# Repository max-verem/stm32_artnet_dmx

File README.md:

# STM32 Art-Net gateway for DMX512

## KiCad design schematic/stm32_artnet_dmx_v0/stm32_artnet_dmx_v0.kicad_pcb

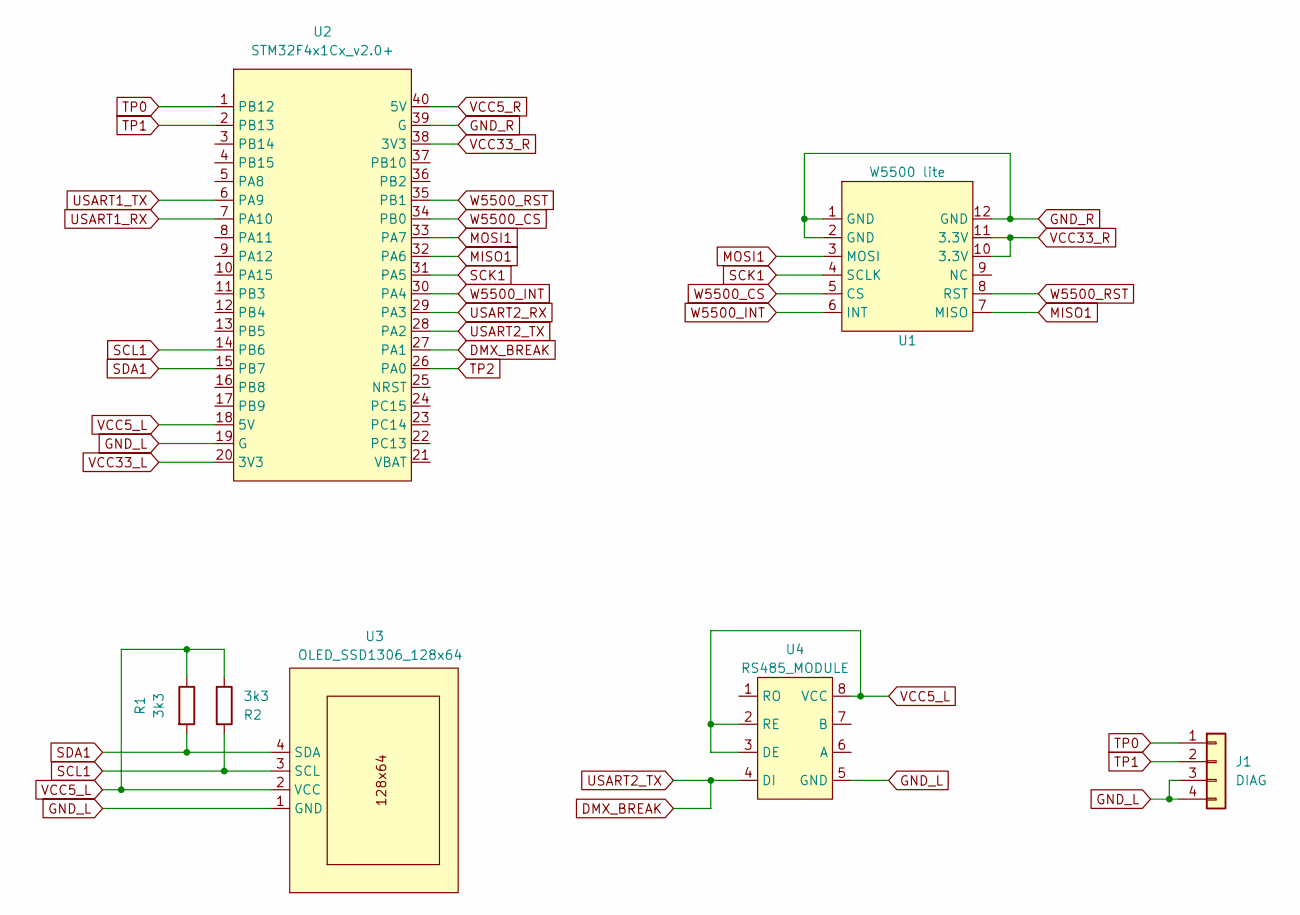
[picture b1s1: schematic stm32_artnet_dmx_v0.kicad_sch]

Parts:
J1: DIAG; PinHeader_1x04_P2.54mm_Vertical
R1, R2: 3k3; R_Axial_DIN0204_L3.6mm_D1.6mm_P7.62mm_Horizontal
U1: W5500 lite; W5500_Lite
U2: STM32F4x1Cx_v2.0+; DIP-40_W15.24mm_LongPads
U3: OLED_SSD1306_128x64
U4: RS485_MODULE

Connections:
DMX_BREAK: U2.27 (PA1), U2.28 (PA2), U4.4 (DI)
GND_L: J1.3, J1.4, U2.19 (G), U3.1 (GND), U4.5 (GND)
GND_R: U1.1 (GND), U1.2 (GND), U1.12 (GND), U2.39 (G)
MISO1: U1.7 (MISO), U2.32 (PA6)
MOSI1: U1.3 (MOSI), U2.33 (PA7)
SCK1: U1.4 (SCLK), U2.31 (PA5)
SCL1: R2.1, U2.14 (PB6), U3.3 (SCL)
SDA1: R1.2, U2.15 (PB7), U3.4 (SDA)
TP0: J1.1, U2.1 (PB12)
TP1: J1.2, U2.2 (PB13)
TP2: U2.26 (PA0)
USART1_RX: U2.7 (PA10)
USART1_TX: U2.6 (PA9)
USART2_RX: U2.29 (PA3)
VCC5_L: R1.1, R2.2, U2.18 (5V), U3.2 (VCC), U4.2 (RE), U4.3 (DE), U4.8 (VCC)
VCC5_R: U2.40 (5V)
VCC33_L: U2.20 (3V3)
VCC33_R: U1.10 (3.3V), U1.11 (3.3V), U2.38 (3V3)
W5500_CS: U1.5 (CS), U2.34 (PB0)
W5500_INT: U1.6 (INT), U2.30 (PA4)
W5500_RST: U1.8 (RST), U2.35 (PB1)

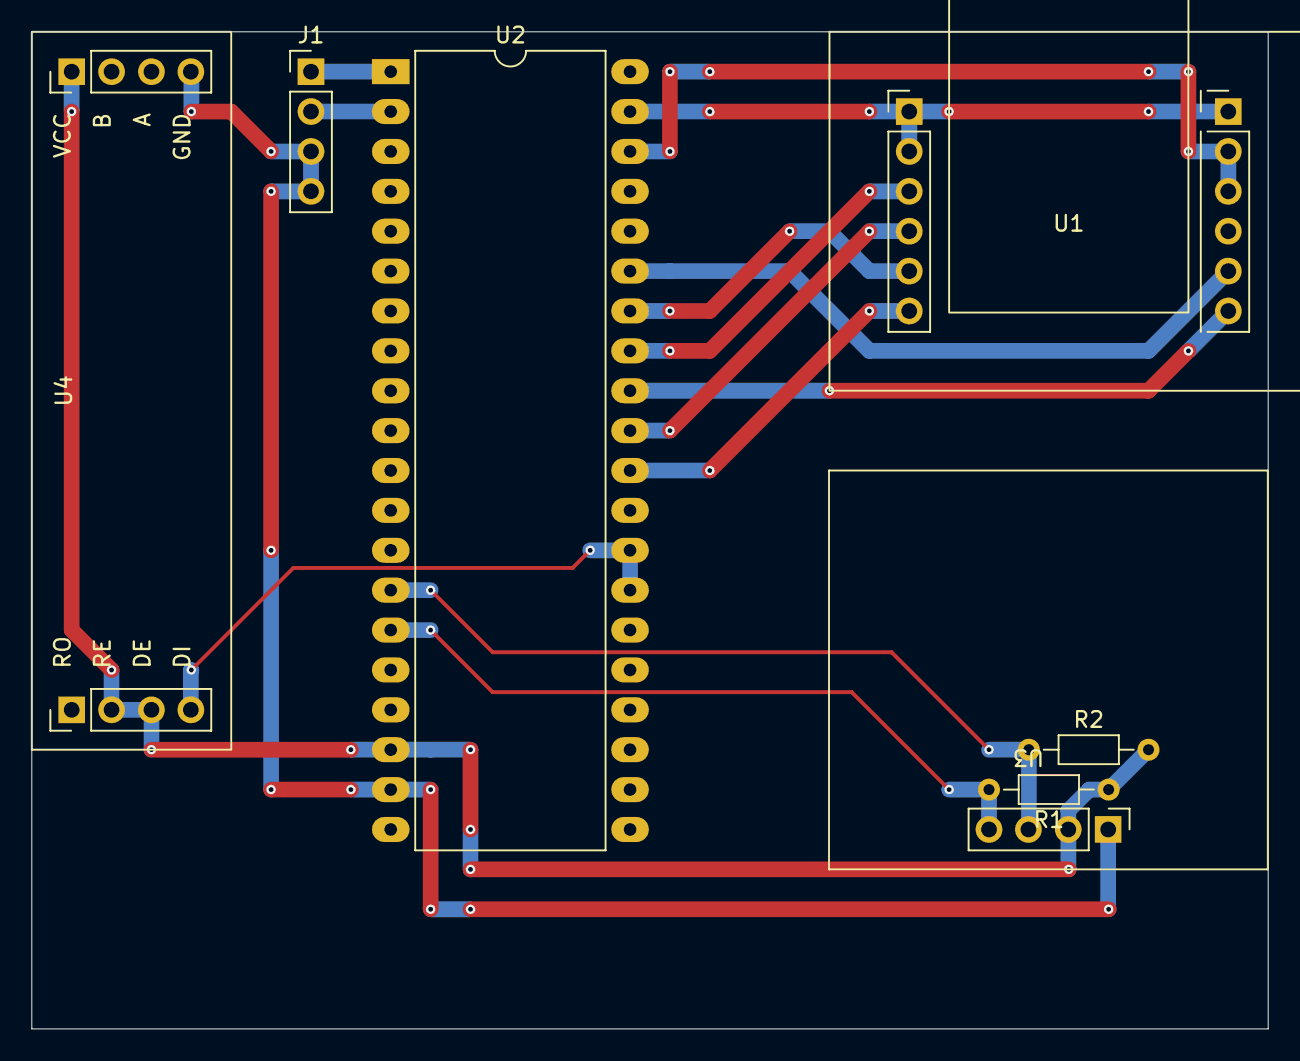
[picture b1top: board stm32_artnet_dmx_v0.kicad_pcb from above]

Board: 2 copper layers, 78.7 x 63.5 mm, 7 parts (0 on the bottom side), 15 nets.

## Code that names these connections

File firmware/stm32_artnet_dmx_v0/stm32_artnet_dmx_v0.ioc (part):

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Mcu.Name=STM32F411C(C-E)Ux
Mcu.Package=UFQFPN48
Mcu.UserName=STM32F411CEUx
PA1.GPIOParameters=GPIO_Speed,PinState,GPIO_PuPd,GPIO_Label,GPIO_ModeDefaultOutputPP
PA1.GPIO_Label=DMX_BREAK
PA1.GPIO_ModeDefaultOutputPP=GPIO_MODE_OUTPUT_OD
PA1.GPIO_PuPd=GPIO_NOPULL
PA1.GPIO_Speed=GPIO_SPEED_FREQ_VERY_HIGH
PA1.PinState=GPIO_PIN_SET
PA1.Signal=GPIO_Output
PA10.Mode=Asynchronous
PA10.Signal=USART1_RX
PA11.Mode=Device_Only
PA11.Signal=USB_OTG_FS_DM
PA12.Mode=Device_Only
PA12.Signal=USB_OTG_FS_DP
PA13.Mode=Serial_Wire
PA13.Signal=SYS_JTMS-SWDIO
PA14.Mode=Serial_Wire
PA14.Signal=SYS_JTCK-SWCLK
PA2.GPIOParameters=GPIO_ModeDefaultPP
PA2.GPIO_ModeDefaultPP=GPIO_MODE_AF_OD
PA2.Mode=Asynchronous
PA2.Signal=USART2_TX
PA3.Mode=Asynchronous
PA3.Signal=USART2_RX
PA4.GPIOParameters=GPIO_PuPd,GPIO_Label
PA4.GPIO_Label=W5500_INT
PA4.GPIO_PuPd=GPIO_PULLUP
PA4.Signal=GPXTI4
PA5.Mode=Full_Duplex_Master
PA5.Signal=SPI1_SCK
PA6.Mode=Full_Duplex_Master
PA6.Signal=SPI1_MISO
PA7.Mode=Full_Duplex_Master
PA7.Signal=SPI1_MOSI
PA9.Mode=Asynchronous
PA9.Signal=USART1_TX
PB0.GPIOParameters=GPIO_Speed,PinState,GPIO_Label
PB0.GPIO_Label=W5500_SCS
PB0.GPIO_Speed=GPIO_SPEED_FREQ_VERY_HIGH
PB0.PinState=GPIO_PIN_SET
PB0.Signal=GPIO_Output
PB1.GPIOParameters=GPIO_Speed,GPIO_Label
PB1.GPIO_Label=W5500_RST
PB1.GPIO_Speed=GPIO_SPEED_FREQ_VERY_HIGH
PB1.Signal=GPIO_Output
PB12.GPIOParameters=GPIO_Speed,GPIO_Label
PB12.GPIO_Label=TP0
PB12.GPIO_Speed=GPIO_SPEED_FREQ_VERY_HIGH
PB12.Signal=GPIO_Output
PB13.GPIOParameters=GPIO_Speed,GPIO_Label
PB13.GPIO_Label=TP1
PB13.GPIO_Speed=GPIO_SPEED_FREQ_VERY_HIGH
PB13.Signal=GPIO_Output
PB6.Mode=I2C
PB6.Signal=I2C1_SCL
PB7.Mode=I2C
PB7.Signal=I2C1_SDA
PC13-ANTI_TAMP.GPIOParameters=PinState,GPIO_PuPd,GPIO_Label,GPIO_ModeDefaultOutputPP
PC13-ANTI_TAMP.GPIO_Label=LED
PC13-ANTI_TAMP.GPIO_ModeDefaultOutputPP=GPIO_MODE_OUTPUT_OD
PC13-ANTI_TAMP.GPIO_PuPd=GPIO_NOPULL
PC13-ANTI_TAMP.PinState=GPIO_PIN_SET
PC13-ANTI_TAMP.Signal=GPIO_Output
PC14-OSC32_IN.Mode=LSE-External-Oscillator
PC14-OSC32_IN.Signal=RCC_OSC32_IN
PC15-OSC32_OUT.Mode=LSE-External-Oscillator
PC15-OSC32_OUT.Signal=RCC_OSC32_OUT
PH0\ -\ OSC_IN.Mode=HSE-External-Oscillator
PH0\ -\ OSC_IN.Signal=RCC_OSC_IN
PH1\ -\ OSC_OUT.Mode=HSE-External-Oscillator
PH1\ -\ OSC_OUT.Signal=RCC_OSC_OUT
RCC.HSE_VALUE=25000000
RCC.SYSCLKFreq_VALUE=96000000
RCC.SYSCLKSource=RCC_SYSCLKSOURCE_PLLCLK
board=custom

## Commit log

2025-05-04 Initial load
